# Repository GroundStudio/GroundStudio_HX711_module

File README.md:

GroundStudio Load Cell Amplifier Module
====================================

Get it from [ardushop.ro](https://ardushop.ro/ro/home/2509-modul-citire-senzor-greutate-hx711-groundstudio.html)

Explore all the GroundStudio products at [GroundStudio.ro](https://groundstudio.ro/)

Description
-------------------
Load cell amplifier module based on HX711 chip.

Contents
-------------------

* [/Documentation](https://github.com/GroundStudio/GroundStudio_HX711_module/tree/main/Documentation) -- Contains documentation written during creation of this repository, with readme.md index of its own!
* [/Firmware](https://github.com/GroundStudio/GroundStudio_HX711_module/tree/main/Firmware) -- Firmware (bootloaders, etc)
* [/Hardware](https://github.com/GroundStudio/GroundStudio_HX711_module/tree/main/Hardware) -- Schematics, layout.
* [/Libraries](https://github.com/GroundStudio/GroundStudio_HX711_module/tree/main/Libraries) -- Arduino/CircuitPython libraries. 
* [/Tools](https://github.com/GroundStudio/GroundStudio_HX711_module/tree/main) -- Tools needed for compiling, uploading bootloader, etc.

Versions
-------------------
*(Not all tags shown)*
* [V0.1] Initial version

License
-------------------

This is released under the [Attribution-ShareAlike 4.0 International (CC BY-SA 4.0)](https://creativecommons.org/licenses/by-sa/4.0/) license. 
**You are welcome to use this for commercial purposes.**

Please consider contributing back to this project or others to help the open-source hardware community continue to thrive and grow! 

Certifications:

[Open Source Hardware Association](https://certification.oshwa.org/ro000016.html)   
   
[
](https://certification.oshwa.org/ro000016.html)

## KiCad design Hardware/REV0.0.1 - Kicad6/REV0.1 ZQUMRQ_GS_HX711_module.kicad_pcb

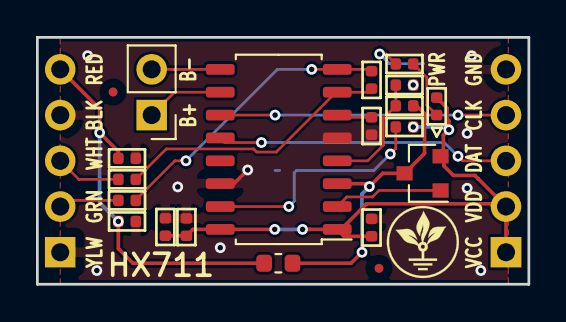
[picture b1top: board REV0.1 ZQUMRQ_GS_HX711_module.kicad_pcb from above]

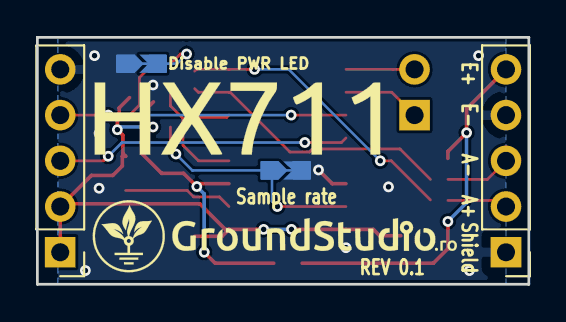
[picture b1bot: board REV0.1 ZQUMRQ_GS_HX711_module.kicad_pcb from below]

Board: 2 copper layers, 27.3 x 13.7 mm, 22 parts (4 on the bottom side), 18 nets.

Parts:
C1, C3, C4, C5, C6: 100nF; C_0402_1005Metric
C2, C7: 10uF; C_0402_1005Metric
D1: RED; LED_0402_1005Metric
J1, J3: Conn_01x05; PinHeader_1x05_P2.54mm_Vertical_Male
J2: SolderJumper_NC
J4: Conn_01x02; PinHeader_1x02_P2.54mm_Vertical_Male
J5: DISABLE PWR LED; SolderJumper_NC
L1: 3.3uH; L_0603_1608Metric
Q1: S8550; SOT-23
R1: 10k; R_0402_1005Metric
R2: 20k; R_0402_1005Metric
R3: 8.2k; R_0402_1005Metric
R4, R5: 100; R_0402_1005Metric
R6: 1k; R_0402_1005Metric
U1: HX711; SOP-16_4.55x10.3mm_P1.27mm

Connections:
GND: C1.1, C2.2, C3.1, C5.1, C6.1, C7.2, J1.1, J1.4, J2.2, J3.5, J5.1, R3.2, U1.5, U1.14
unnamed: C1.2, C2.1, J1.5, L1.1
unnamed: C3.2, U1.6
unnamed: C4.1, R4.1, U1.7
unnamed: C4.2, R5.2, U1.8
unnamed: D1.1, R6.1
unnamed: J1.2, R5.1
unnamed: J1.3, R4.2
unnamed: J2.1, R1.1, U1.15
unnamed: J3.3, U1.12
unnamed: J3.4, U1.11
unnamed: J4.1, U1.10
unnamed: J4.2, U1.9
unnamed: J5.2, R6.2
unnamed: L1.2, Q1.3, R2.1, U1.3
unnamed: Q1.1, U1.2
unnamed: R2.2, R3.1, U1.4
VCC: C5.2, C6.2, C7.1, D1.2, J3.1, J3.2, Q1.2, R1.2, U1.1, U1.16

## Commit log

2023-10-24 - first commit
2023-11-03 - added datasheet
